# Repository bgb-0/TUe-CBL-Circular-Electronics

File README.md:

# :recycle: Prototype Audio PCB for TU/e 4CBLW00-11 course
This repository contains the PCB design files (KiCad 9), schematic, and 3D model image
for a prototype modular bluetooth audio board, based on te ESP32-Mini-1 module.
This is a prototype PCB designed for a modular bluetooth speaker, for the Multidisciplinary CBL (4CBLW00) course of year 2024/2025, made possible with help from Darije Caic.
<div align="center">
  
</div>

## :round_pushpin: Features
- ESP32-MINI-1 module for bluetooth connectivity and low-power
- Detacheable speaker and battery
- USB-C power delivery
- Small form factor (45 x 40 mm)
## :card_file_box: Contents
- PCB design files: The KiCad project files for the PCB design.
- Schematic: The circuit diagram of the design.
- 3D model image: A preview image of the 3D model of the board.
## :pencil2: Schematic 
<div align="center">
  
</div>

## :triangular_ruler: Lay-out
<div align="center">
  
</div>

## :hammer_and_wrench: License
This hardware design is licensed under the CERN Open Hardware Licence Version 2
 – Permissive, as approved by the Technische Universiteit Eindhoven (TU/e).

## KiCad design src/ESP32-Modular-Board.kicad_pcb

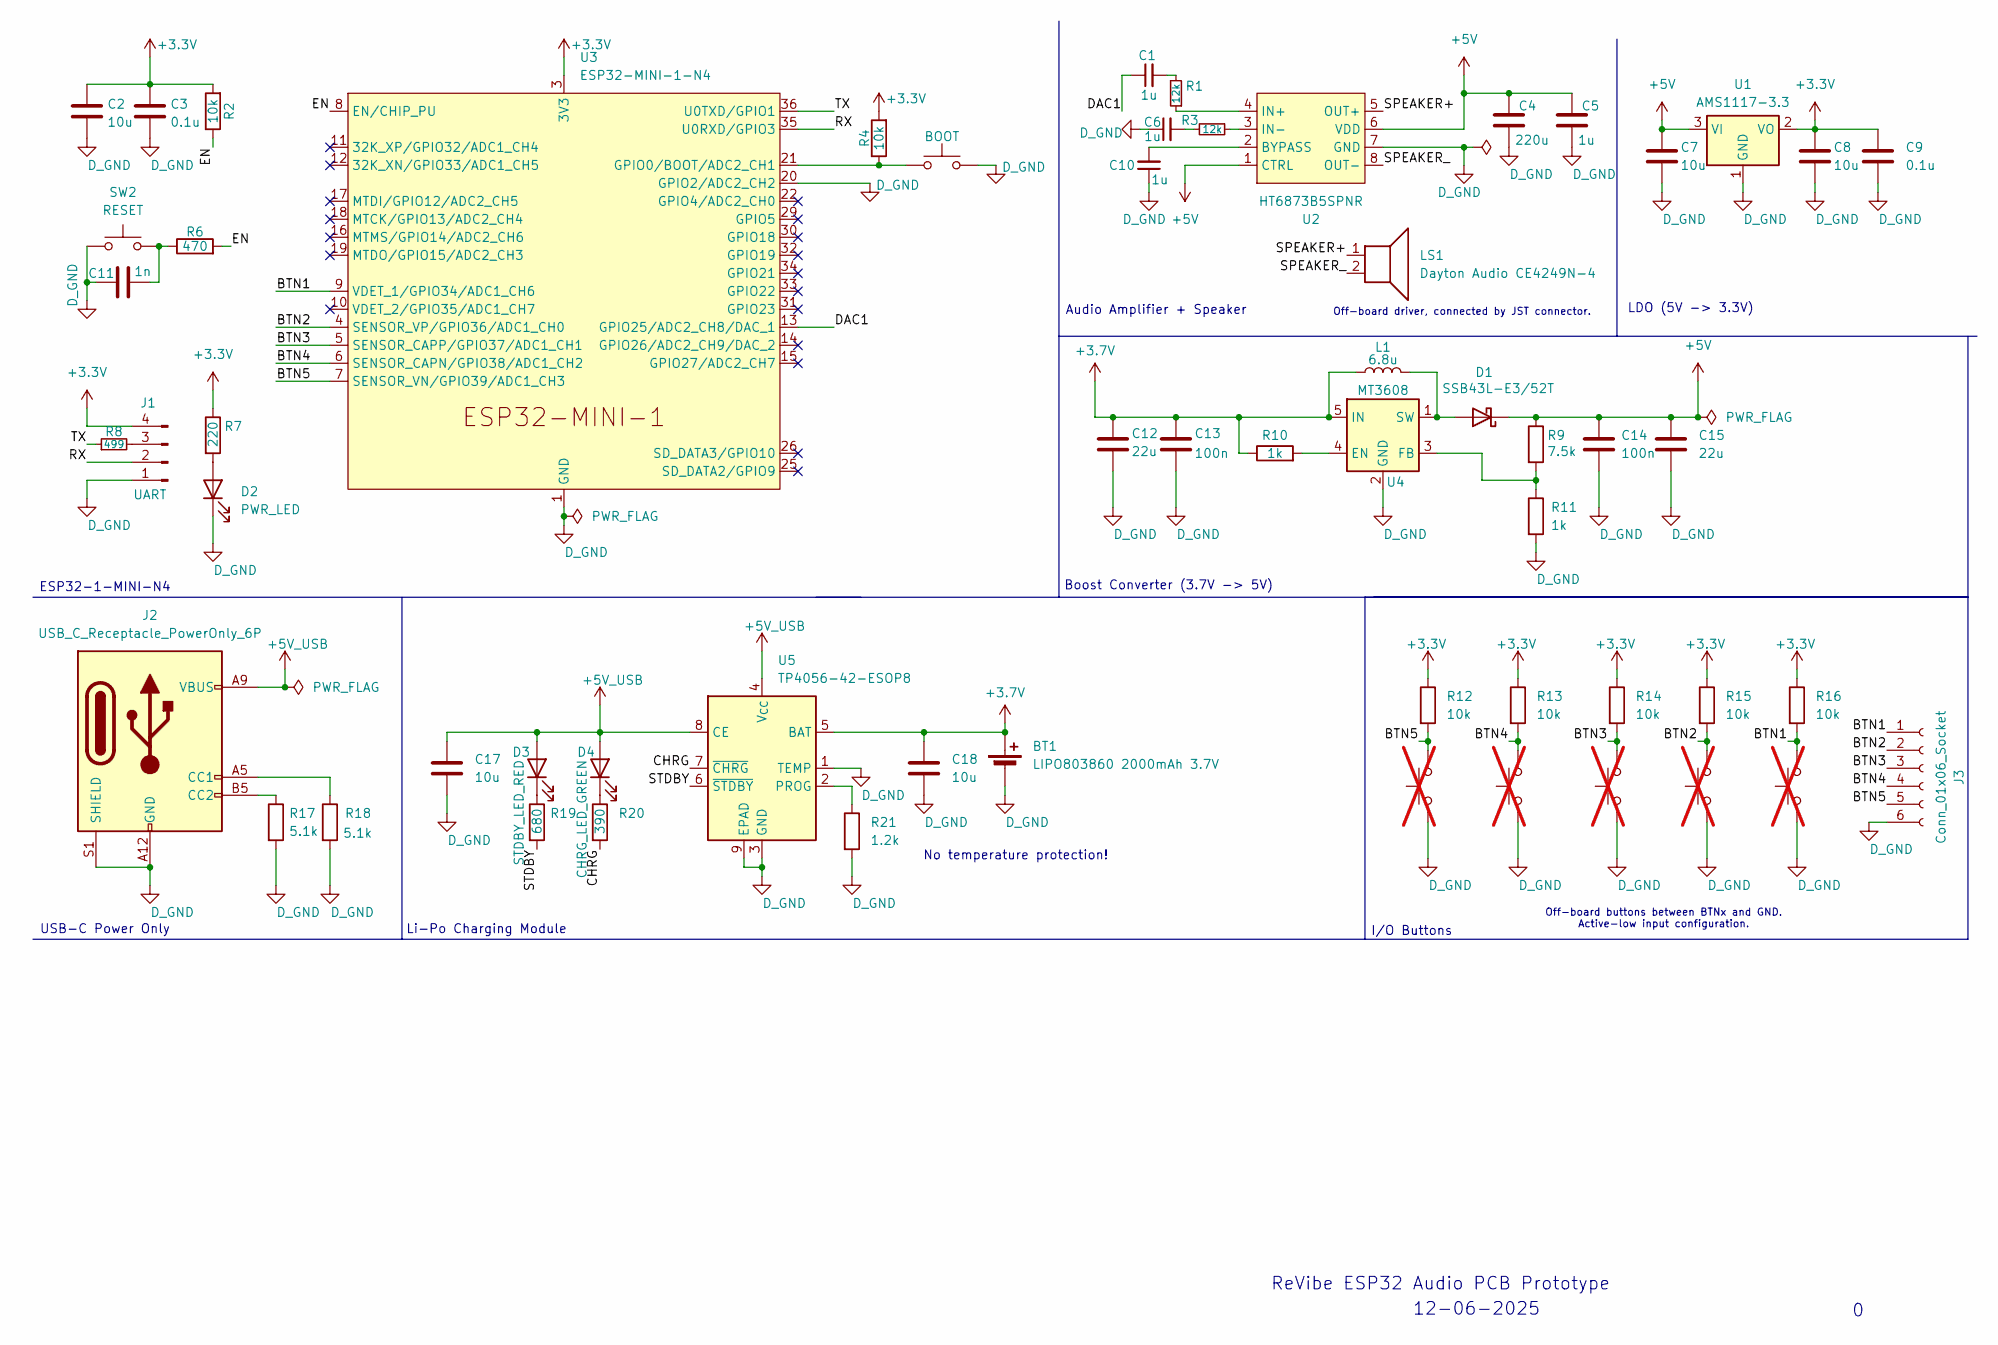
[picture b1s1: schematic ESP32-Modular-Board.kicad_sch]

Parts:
BT1: LIPO803860 2000mAh 3.7V; JST_PH_B2B-PH-K_1x02_P2.00mm_Vertical
C1, C5, C6, C10: 1u; C_0603_1608Metric
C2: 10u; C_0805_2012Metric
C3: 0.1u; C_0402_1005Metric
C4: 220u; C_Elec_6.3x5.8
C7, C8: 10u; C_1206_3216Metric
C9: 0.1u; C_1206_3216Metric
C11: 1n; C_0402_1005Metric
C12, C15: 22u; C_1210_3225Metric
C13, C14: 100n; C_0402_1005Metric
C17, C18: 10u; C_0402_1005Metric
D1: SSB43L-E3/52T; D_SMB
D2: PWR_LED; LED_0805_2012Metric
D3: STDBY_LED_RED; LED_0805_2012Metric
D4: CHRG_LED_GREEN; LED_0805_2012Metric
J1: UART; PinHeader_1x04_P2.54mm_Vertical
J2: USB_C_Receptacle_PowerOnly_6P; USB_C_Receptacle_GCT_USB4125-xx-x-0190_6P_TopMnt_Horizontal
J3: Conn_01x06_Socket; JST_PH_B6B-PH-K_1x06_P2.00mm_Vertical
L1: 6.8u; L_TDK_VLS6045EX_VLS6045AF
LS1: Dayton Audio CE4249N-4; JST_PH_B2B-PH-K_1x02_P2.00mm_Vertical
R1, R3: 12k; R_0805_2012Metric
R2, R4, R12, R13, R14, R15, R16: 10k; R_0805_2012Metric
R6: 470; R_0805_2012Metric
R7: 220; R_0805_2012Metric
R8: 499; R_0805_2012Metric
R9: 7.5k; R_0805_2012Metric
R10, R11: 1k; R_0805_2012Metric
R17, R18: 5.1k; R_0603_1608Metric
R19: 680; R_0805_2012Metric
R20: 390; R_0805_2012Metric
R21: 1.2k; R_0805_2012Metric
SW1: BOOT; SW_Push_SPST_NO_Alps_SKRK
SW2: RESET; SW_Push_SPST_NO_Alps_SKRK
SW3, SW4, SW5, SW6, SW7: SW_Push; not fitted
U1: AMS1117-3.3; SOT-223-3_TabPin2
U2: HT6873B5SPNR; SOP-8_3.9x4.9mm_P1.27mm
U3: ESP32-MINI-1-N4; ESP32-MINI-1
U4: MT3608; SOT-23-6
U5: TP4056-42-ESOP8; SOIC-8-1EP_3.9x4.9mm_P1.27mm_EP2.41x3.3mm_ThermalVias

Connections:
+3.3V: C2.1, C3.1, C8.1, C9.1, J1.4, R2.2, R4.2, R7.1, R12.1, R13.1, R14.1, R15.1, R16.1, U1.2 (VO), U3.3 (3V3)
+3.7V: BT1.1 (+), C12.1, C13.1, C18.1, L1.1, R10.1, U4.5 (IN), U5.5 (BAT)
+5V: C4.1, C5.1, C7.1, C14.1, C15.1, D1.1 (K), R9.1, U1.3 (VI), U2.1 (CTRL), U2.6 (VDD)
+5V_USB: C17.1, D3.2 (A), D4.2 (A), J2.A9 (VBUS), J2.B9 (VBUS), U5.4 (V_{CC}), U5.8 (CE)
/BTN1: J3.1, R16.2, SW7.2, U3.9 (VDET_1/GPIO34/ADC1_CH6)
/BTN2: J3.2, R15.2, SW6.2, U3.4 (SENSOR_VP/GPIO36/ADC1_CH0)
/BTN3: J3.3, R14.2, SW5.2, U3.5 (SENSOR_CAPP/GPIO37/ADC1_CH1)
/BTN4: J3.4, R13.2, SW4.2, U3.6 (SENSOR_CAPN/GPIO38/ADC1_CH2)
/BTN5: J3.5, R12.2, SW3.2, U3.7 (SENSOR_VN/GPIO39/ADC1_CH3)
/CHRG: R20.2, U5.7 (~CHRG)
/DAC1: C1.1, U3.13 (GPIO25/ADC2_CH8/DAC_1)
/EN: R2.1, R6.2, U3.8 (EN/CHIP_PU)
/RX: J1.2, U3.35 (U0RXD/GPIO3)
/SPEAKER+: LS1.1, U2.5 (OUT+)
/SPEAKER_: LS1.2, U2.8 (OUT-)
/STDBY: R19.2, U5.6 (~STDBY)
/TX: R8.1, U3.36 (U0TXD/GPIO1)
D_GND: BT1.2 (-), C2.2, C3.2, C4.2, C5.2, C6.1, C7.2, C8.2, C9.2, C10.1, C11.1, C12.2, C13.2, C14.2, C15.2, C17.2, C18.2, D2.1 (K), J1.1, J2.A12 (GND), J2.B12 (GND), J2.S1 (SHIELD), J3.6, R11.2, R17.2, R18.2, R21.2, SW1.2, SW2.1, SW3.1, SW4.1, SW5.1, SW6.1, SW7.1, U1.1 (GND), U2.7 (GND), U3.1 (GND), U3.2 (GND), U3.20 (GPIO2/ADC2_CH2), U3.27 (GND), U3.38 (GND), U3.39 (GND), U3.40 (GND), U3.41 (GND), U3.42 (GND), U3.43 (GND), U3.44 (GND), U3.45 (GND), U3.46 (GND), U3.47 (GND), U3.48 (GND), U3.49 (GND), U3.50 (GND), U3.51 (GND), U3.52 (GND), U3.53 (GND), U3.54 (GND), U3.55 (GND), U4.2 (GND), U5.1 (TEMP), U5.3 (GND), U5.9 (EPAD)
unnamed: C1.2, R1.2
unnamed: C6.2, R3.2
unnamed: C11.2, R6.1, SW2.2
unnamed: D1.2 (A), L1.2, U4.1 (SW)
unnamed: D2.2 (A), R7.2
unnamed: D3.1 (K), R19.1
unnamed: D4.1 (K), R20.1
unnamed: J1.3, R8.2
unnamed: J2.A5 (CC1), R18.1
unnamed: J2.B5 (CC2), R17.1
unnamed: C10.2, U2.2 (BYPASS)
unnamed: R1.1, U2.4 (IN+)
unnamed: R3.1, U2.3 (IN-)
unnamed: R4.1, SW1.1, U3.21 (GPIO0/BOOT/ADC2_CH1)
unnamed: R10.2, U4.4 (EN)
unnamed: R9.2, R11.1, U4.3 (FB)
unnamed: R21.1, U5.2 (PROG)

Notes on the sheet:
Boost Converter (3.7V -> 5V)
Li-Po Charging Module
Off-board buttons between BTNx and GND. Active-low input configuration.
No temperature protection!
12-06-2025
ReVibe ESP32 Audio PCB Prototype
USB-C Power Only
LDO (5V -> 3.3V)
ESP32-1-MINI-N4
Off-board driver, connected by JST connector.
Audio Amplifier + Speaker
I/O Buttons

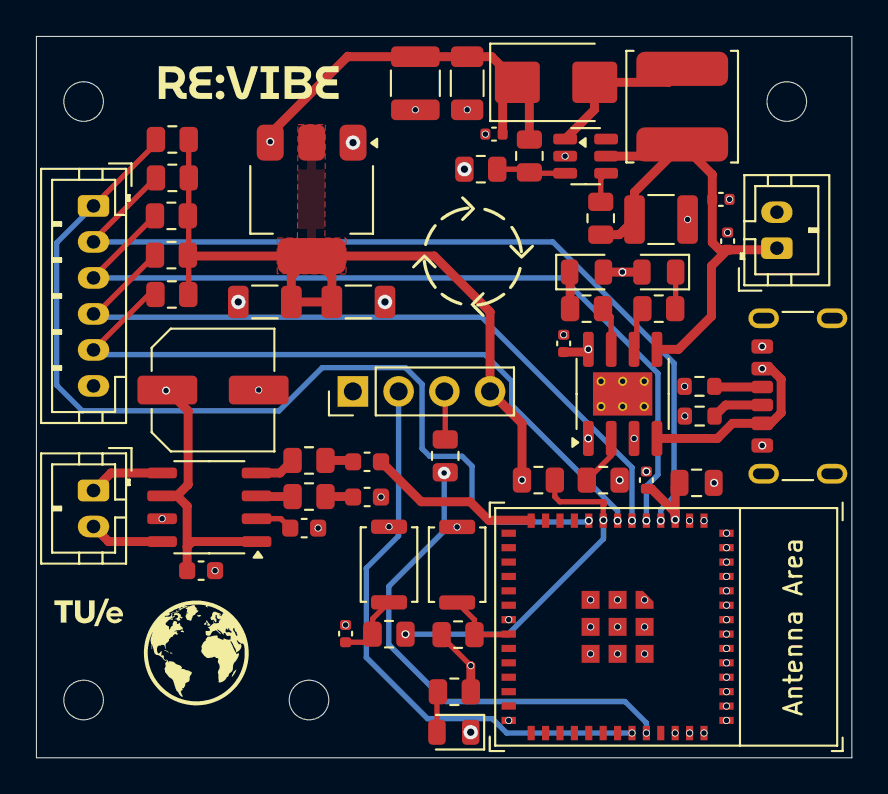
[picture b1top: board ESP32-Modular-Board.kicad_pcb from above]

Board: 4 copper layers, 45.3 x 40.1 mm, 58 parts (0 on the bottom side), 35 nets.

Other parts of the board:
M2_1, M2_2, M2_3, M2_4: MountingHole_2.2mm_M2

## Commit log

2025-06-14 Initial PCB design for TU/e 2024/2025 CBL Circular Electronics
2025-06-14 Reorganized file structure
2025-06-14 Added pictures
2025-06-14 Add picture of schematic
2025-06-14 Add CERN CERN Open Hardware Licence Version 2
